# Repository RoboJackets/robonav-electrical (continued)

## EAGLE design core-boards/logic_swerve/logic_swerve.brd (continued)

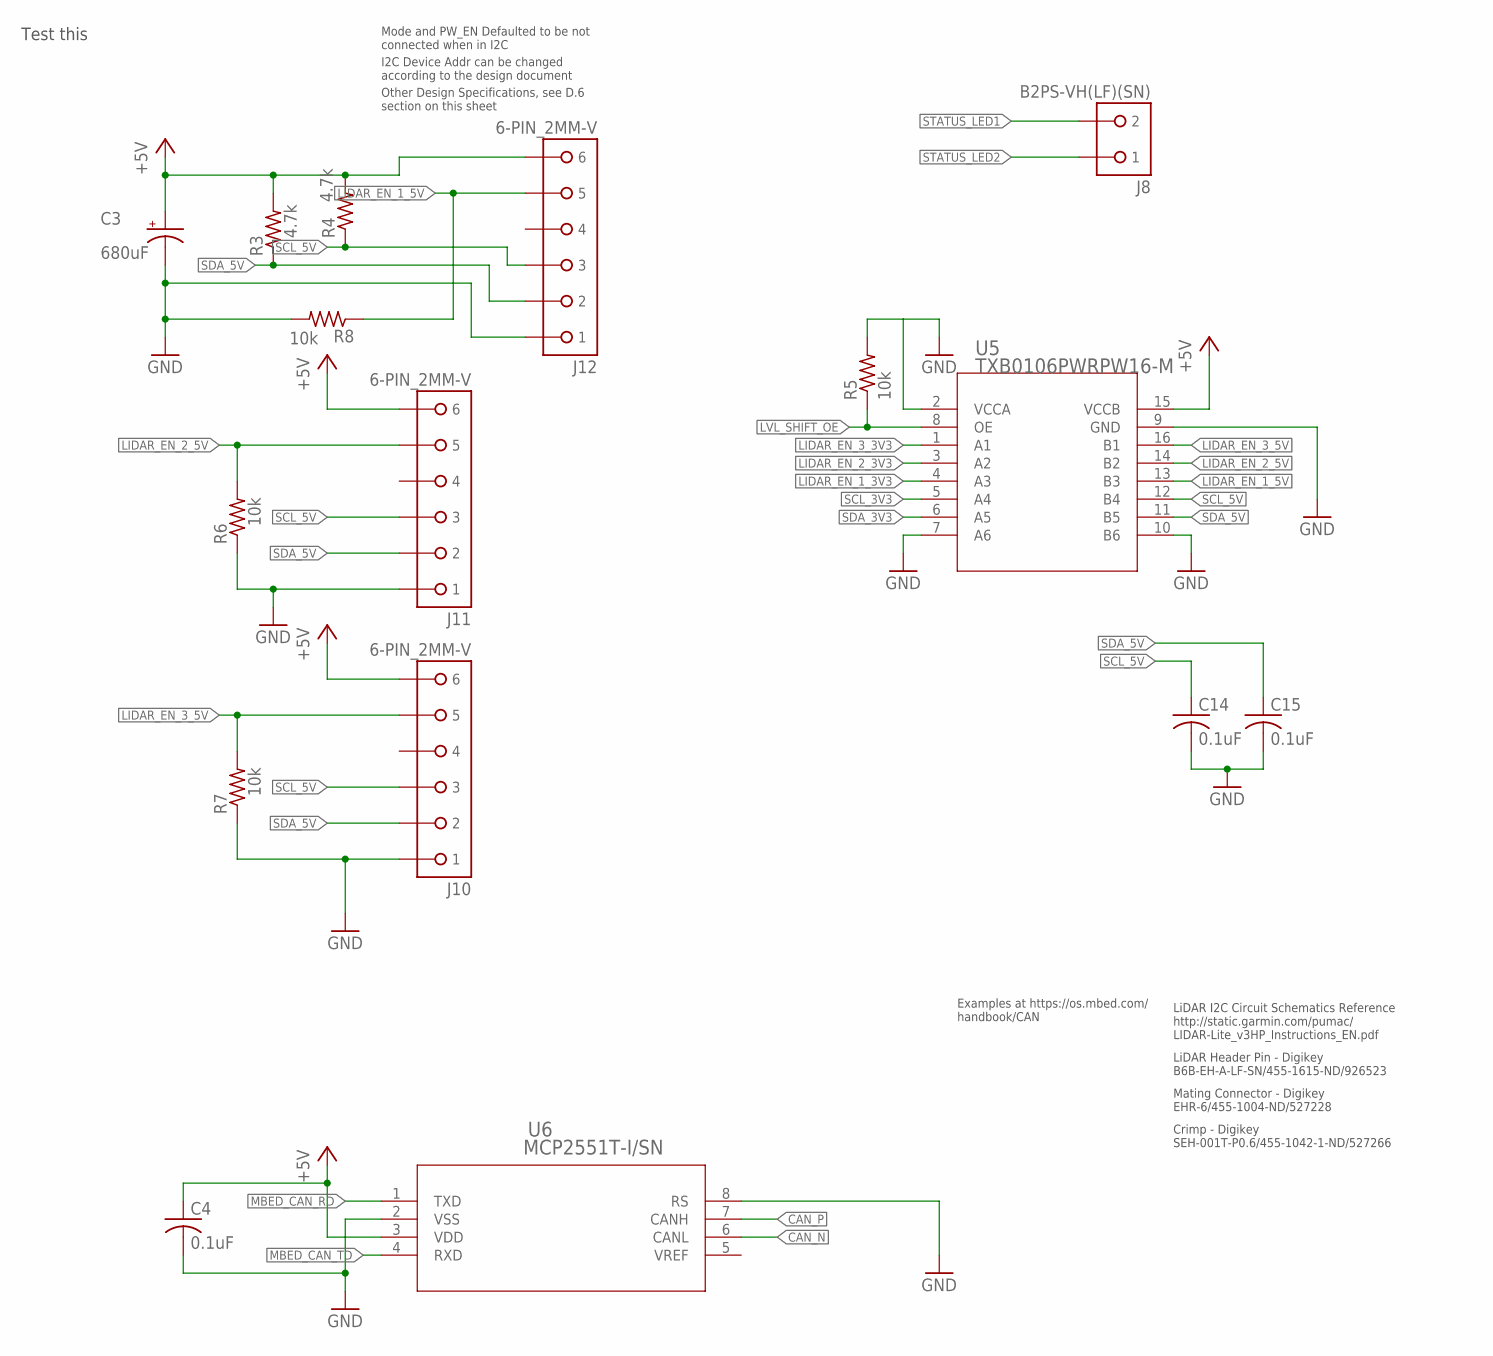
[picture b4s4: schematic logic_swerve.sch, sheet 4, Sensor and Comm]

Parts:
C3: 680uF; E5-5
C4, C14, C15: 0.1uF; C0603
J8: B2PS-VH(LF)(SN); B2PS-CENTERED
J10, J11, J12: 6-PIN_2MM-V; 2MM-6-V
R3, R4: 4.7k; R0603
R5, R6, R7, R8: 10k; R0603
U5: TXB0106PWRPW16-M; PW16-M
U6: MCP2551T-I/SN; SOIC8-N_MC

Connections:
+5V: C3.+, C4.1, J10.6, J11.6, J12.6, R3.2, R4.2, U5.15 (VCCB), U6.3 (VDD); also elsewhere on the board
CAN_N: U6.6 (CANL); also elsewhere on the board
CAN_P: U6.7 (CANH); also elsewhere on the board
GND: C3.-, C4.2, C14.2, C15.2, J10.1, J11.1, J12.1, R5.2, R6.1, R7.1, R8.2, U5.2 (VCCA), U5.7 (A6), U5.9 (GND), U5.10 (B6), U6.2 (VSS), U6.8 (RS); also elsewhere on the board
LIDAR_EN_1_3V3: U5.4 (A3); also elsewhere on the board
LIDAR_EN_1_5V: J12.5, R8.1, U5.13 (B3)
LIDAR_EN_2_3V3: U5.3 (A2); also elsewhere on the board
LIDAR_EN_2_5V: J11.5, R6.2, U5.14 (B2)
LIDAR_EN_3_3V3: U5.1 (A1); also elsewhere on the board
LIDAR_EN_3_5V: J10.5, R7.2, U5.16 (B1)
LVL_SHIFT_OE: R5.1, U5.8 (OE); also elsewhere on the board
MBED_CAN_RD: U6.1 (TXD); also elsewhere on the board
MBED_CAN_TD: U6.4 (RXD); also elsewhere on the board
SCL_3V3: U5.5 (A4); also elsewhere on the board
SCL_5V: C14.1, J10.3, J11.3, J12.3, R4.1, U5.12 (B4)
SDA_3V3: U5.6 (A5); also elsewhere on the board
SDA_5V: C15.1, J10.2, J11.2, J12.2, R3.1, U5.11 (B5)
STATUS_LED1: J8.2; also elsewhere on the board
STATUS_LED2: J8.1; also elsewhere on the board

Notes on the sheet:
LiDAR I2C Circuit Schematics Reference http://static.garmin.com/pumac/ LIDAR-Lite_v3HP_Instructions_EN.pdf
I2C Device Addr can be changed according to the design document
LiDAR Header Pin - Digikey B6B-EH-A-LF-SN/455-1615-ND/926523
Mating Connector - Digikey EHR-6/455-1004-ND/527228
Crimp - Digikey SEH-001T-P0.6/455-1042-1-ND/527266
Mode and PW_EN Defaulted to be not connected when in I2C
Examples at https://os.mbed.com/ handbook/CAN
Other Design Specifications, see D.6 section on this sheet
Test this

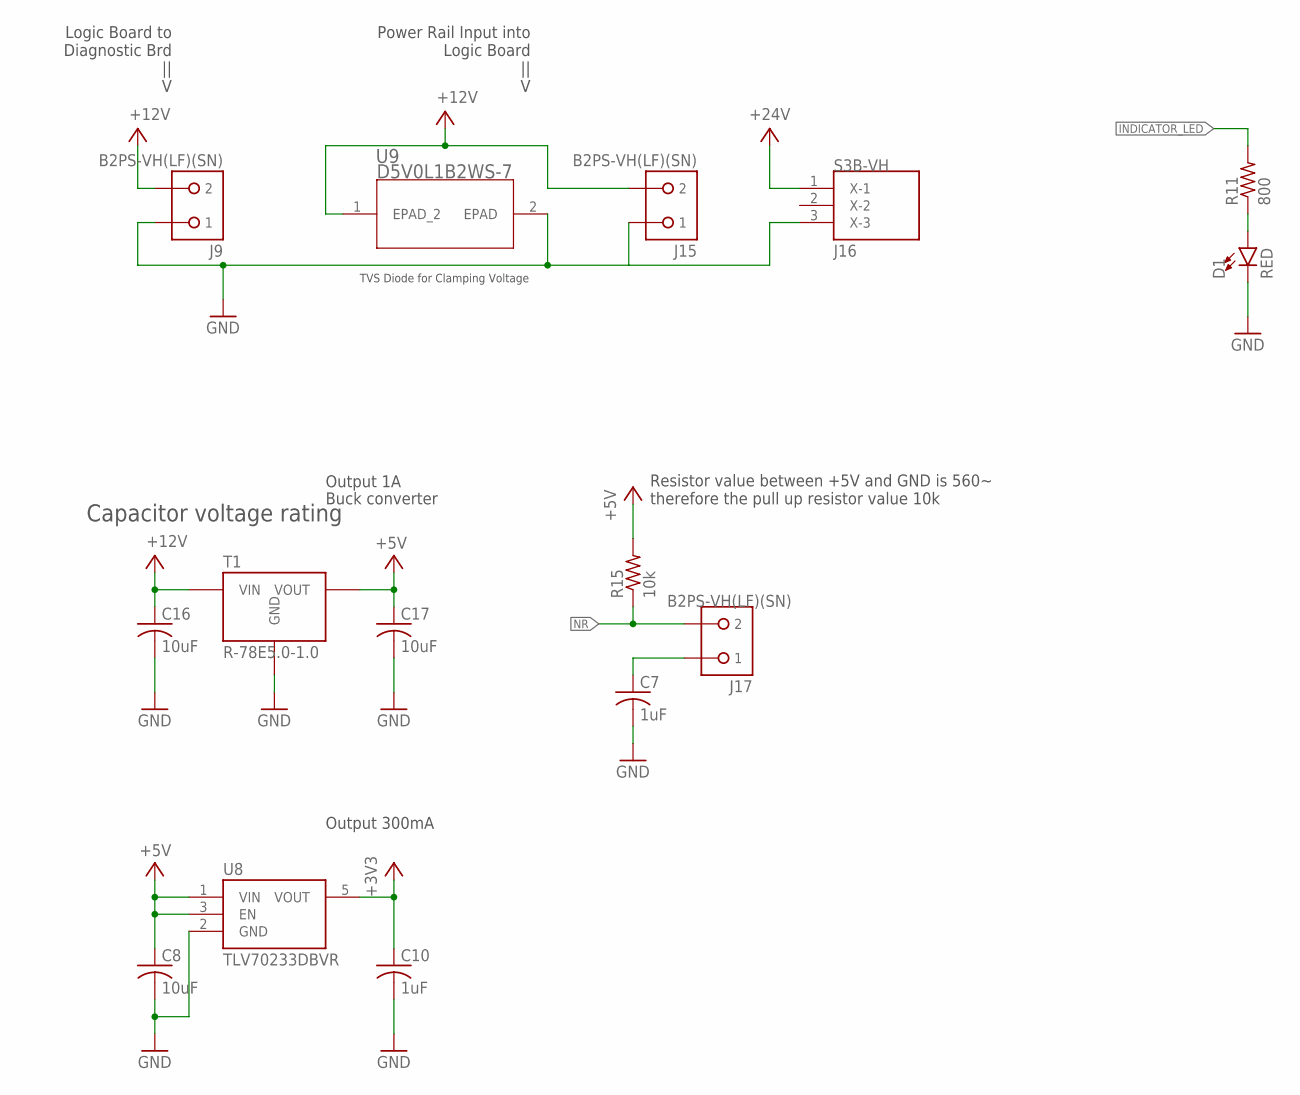
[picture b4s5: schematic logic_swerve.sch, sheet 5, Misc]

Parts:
C7, C10: 1uF; C0805
C8, C16, C17: 10uF; C0805
D1: RED; LED-0603
J9, J15, J17: B2PS-VH(LF)(SN); B2PS-CENTERED
J16: S3B-VH
R11: 800; R0603
R15: 10k; R0603
T1: R-78E5.0-1.0; R-78E
U8: TLV70233DBVR; SOT-23-5
U9: D5V0L1B2WS-7; SOD323

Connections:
+3V3: C10.1, U8.5 (VOUT); also elsewhere on the board
+5V: C8.1, C17.1, R15.2, T1.3 (VOUT), U8.1 (VIN), U8.3 (EN); also elsewhere on the board
+12V: C16.1, J9.2, J15.2, T1.1 (VIN), U9.1 (EPAD_2); also elsewhere on the board
+24V: J16.1 (X-1); also elsewhere on the board
GND: C7.2, C8.2, C10.2, C16.2, C17.2, D1.C, J9.1, J15.1, J16.3 (X-3), T1.2 (GND), U8.2 (GND), U9.2 (EPAD); also elsewhere on the board
INDICATOR_LED: R11.2; also elsewhere on the board
unnamed: D1.A, R11.1
unnamed: C7.1, J17.1
NR: J17.2, R15.1; also elsewhere on the board

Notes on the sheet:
Buck converter
Output 1A
Output 300mA
Power Rail Input into Logic Board || V
Logic Board to Diagnostic Brd || V
Capacitor voltage rating
Resistor value between +5V and GND is 560~ therefore the pull up resistor value 10k
TVS Diode for Clamping Voltage

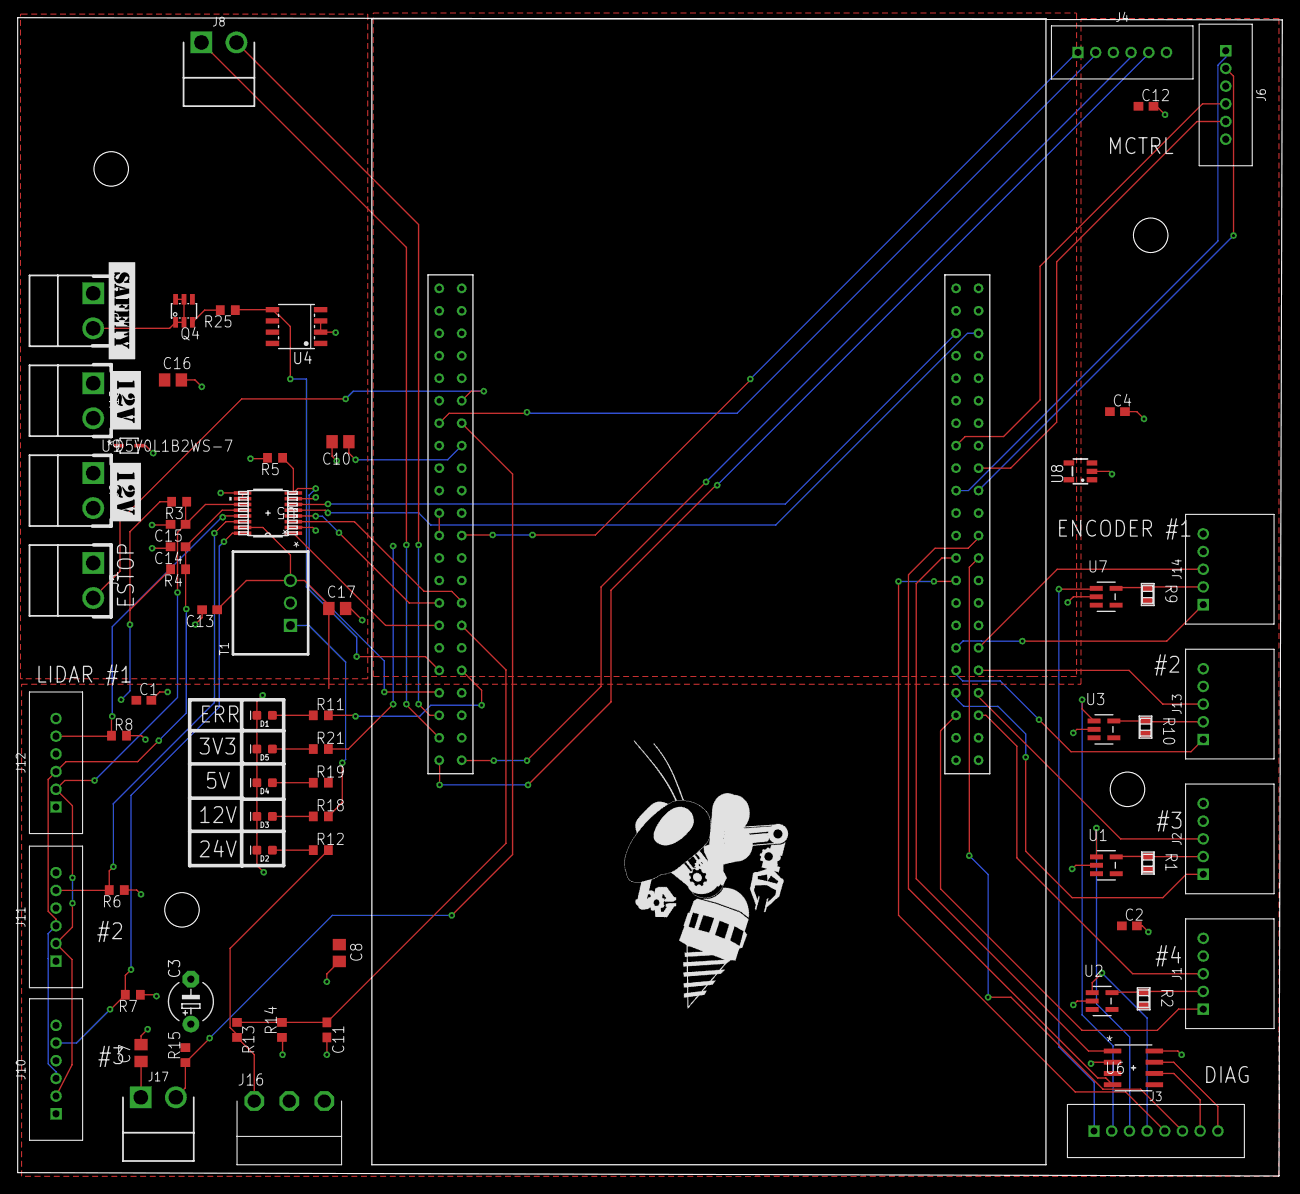
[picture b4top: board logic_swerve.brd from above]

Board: 2 copper layers, 142.9 x 130.9 mm, 75 parts (0 on the bottom side), 61 nets.

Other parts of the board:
U$2, U$3, U$4, U$5: STANDOFF-HOLE
U$6, U$7: 12V
U$10: ROBOBUZZ_1.4X
U$12: SAFETY

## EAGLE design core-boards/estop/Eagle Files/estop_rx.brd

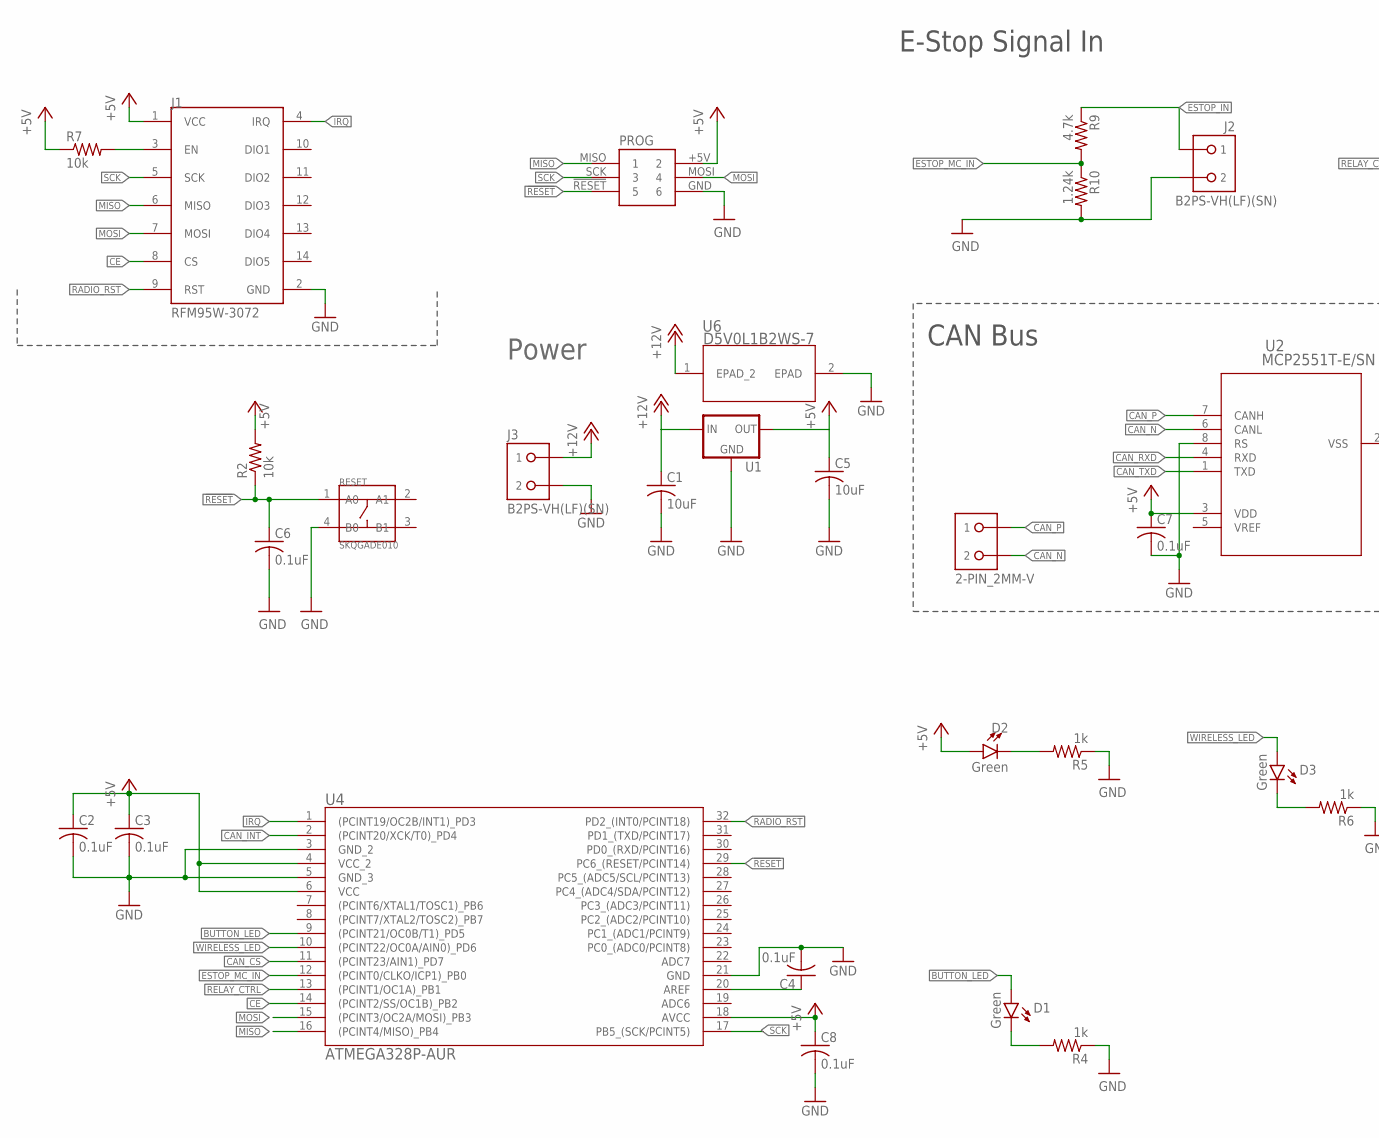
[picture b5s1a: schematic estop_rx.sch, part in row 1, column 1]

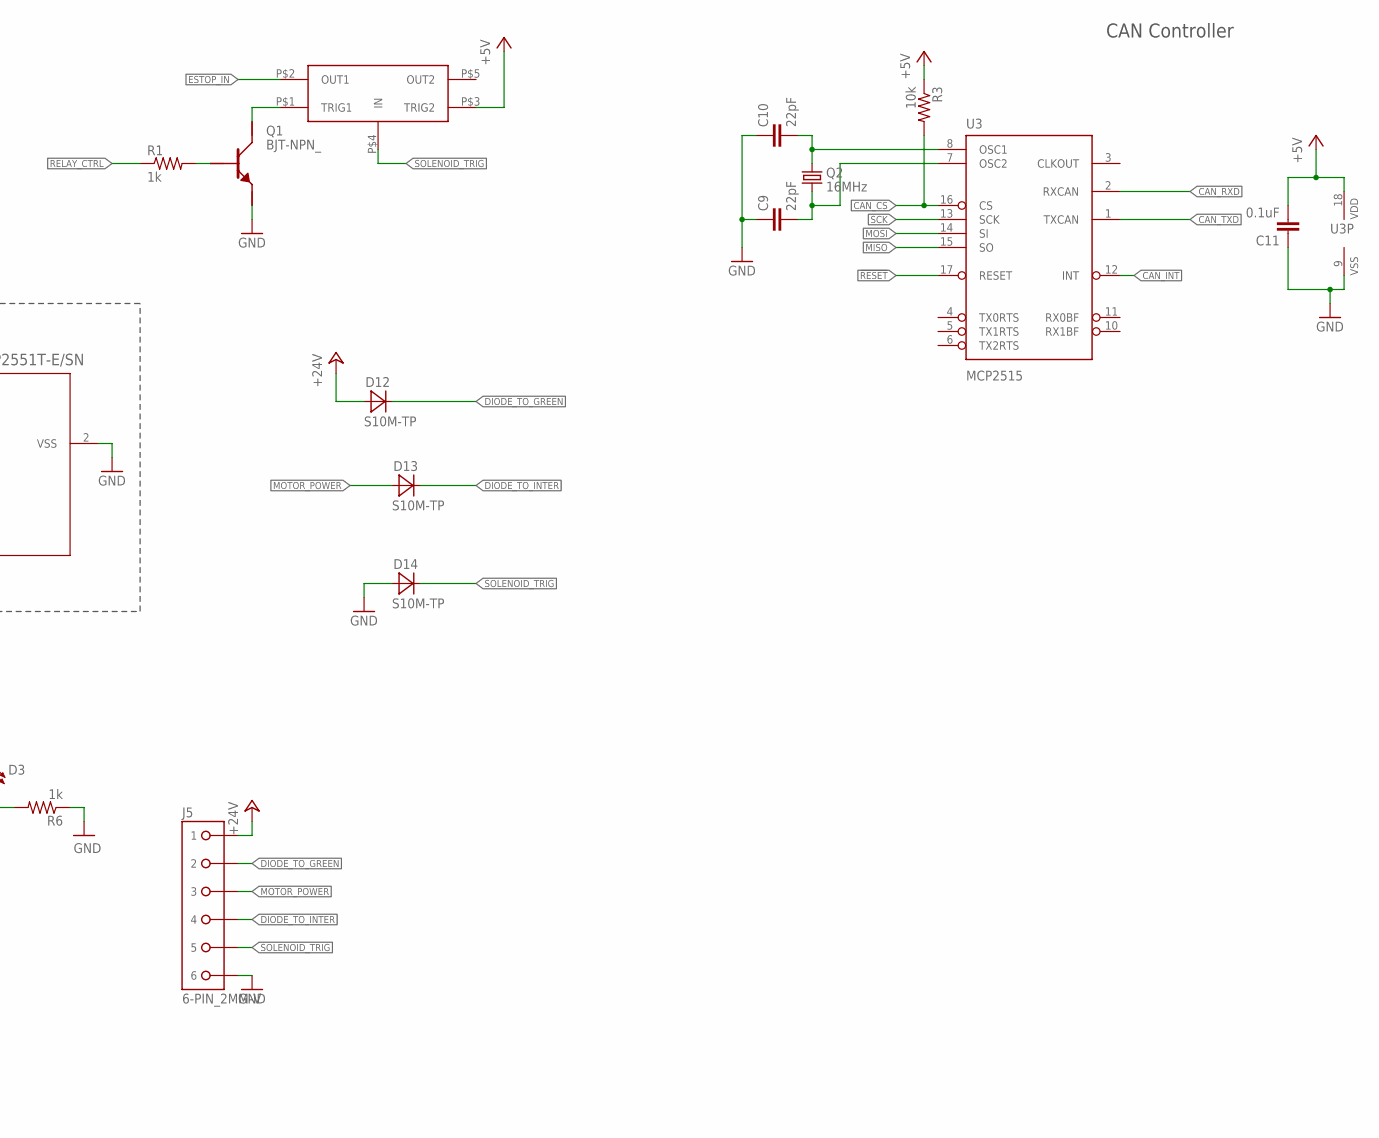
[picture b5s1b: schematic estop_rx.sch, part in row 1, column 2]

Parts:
C1, C5: 10uF; C0805
C2, C3, C4, C6, C7, C8: 0.1uF; C0603
C9, C10: 22pF; 0603-CAP
C11: 0.1uF; 0603-CAP
D1, D2, D3: Green; LED-0603
D12, D13, D14: S10M-TP; SMC
J1: RFM95W-3072
J2, J3: B2PS-VH(LF)(SN); B2PS-CENTERED
J4: 2-PIN_2MM-V; 2MM-2-V
J5: 6-PIN_2MM-V; 2MM-6-V
PROG: ICSP Connector; 2X3SHROUDED
Q1: BJT-NPN_; SOT-23-3
Q2: 16MHz; CRYSTAL-SMD-5X3
R1, R4, R5, R6: 1k; R0603
R2, R3, R7: 10k; R0603
R9: 4.7k; R0603
R10: 1.24k; R0603
RESET: SKQGADE010; SW4-SMD-5.2X5.2X1.5MM
U1: R-78E5.0-1.0CONV_R-78E5.0-1.0; CONV_R-78E5.0-1.0
U2: MCP2551T-E/SN; SOIC8-N_MC
U3: MCP2515; SO-18W
U4: ATMEGA328P-AUR
U6: D5V0L1B2WS-7; SOD323
U$1: G5LE-14

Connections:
!RESET: C6.1, PROG.!RESET (5), R2.1, RESET.1 (A0), U3.17 (RESET), U4.29 (PC6_(RESET/PCINT14))
+5V: C2.1, C3.1, C5.1, C7.1, C8.1, C11.2, D2.A, J1.1 (VCC), PROG.+5V (2), R2.2, R3.1, R7.1, U1.3 (OUT), U2.3 (VDD), U3.18 (VDD), U4.4 (VCC_2), U4.6 (VCC), U4.18 (AVCC), U$1.P$3 (TRIG2)
+12V: C1.1, J3.1, U1.1 (IN), U6.1 (EPAD_2)
+24V: D12.A, J5.1
BUTTON_LED: D1.A, U4.9 ((PCINT21/OC0B/T1)_PD5)
CAN_CS: R3.2, U3.16 (CS), U4.11 ((PCINT23/AIN1)_PD7)
CAN_INT: U3.12 (INT), U4.2 ((PCINT20/XCK/T0)_PD4)
CAN_N: J4.2, U2.6 (CANL)
CAN_P: J4.1, U2.7 (CANH)
CAN_RXD: U2.4 (RXD), U3.2 (RXCAN)
CAN_TXD: U2.1 (TXD), U3.1 (TXCAN)
CE: J1.8 (CS), U4.14 ((PCINT2/SS/OC1B)_PB2)
DIODE_TO_GREEN: D12.C, J5.2
DIODE_TO_INTER: D13.C, J5.4
ESTOP_IN: J2.1, R9.1, U$1.P$2 (OUT1)
ESTOP_MC_IN: R9.2, R10.1, U4.12 ((PCINT0/CLKO/ICP1)_PB0)
GND: C1.2, C2.2, C3.2, C4.2, C5.2, C6.2, C7.2, C8.2, C9.1, C10.1, C11.1, D14.A, J1.2 (GND), J2.2, J3.2, J5.6, PROG.GND (6), Q1.2 (E), R4.1, R5.1, R6.1, R10.2, RESET.4 (B0), U1.2 (GND), U2.2 (VSS), U2.8 (RS), U3.9 (VSS), U4.3 (GND_2), U4.5 (GND_3), U4.21 (GND), U6.2 (EPAD)
IRQ: J1.4 (IRQ), U4.1 ((PCINT19/OC2B/INT1)_PD3)
MISO: J1.6 (MISO), PROG.MISO (1), U3.15 (SO), U4.16 ((PCINT4/MISO)_PB4)
MOSI: J1.7 (MOSI), PROG.MOSI (4), U3.14 (SI), U4.15 ((PCINT3/OC2A/MOSI)_PB3)
MOTOR_POWER: D13.A, J5.3
unnamed: Q1.3 (C), U$1.P$1 (TRIG1)
unnamed: D2.C, R5.2
unnamed: D1.C, R4.2
unnamed: D3.C, R6.2
unnamed: Q1.1 (B), R1.2
unnamed: J1.3 (EN), R7.2
unnamed: C4.1, U4.20 (AREF)
unnamed: C10.2, Q2.3 (2), U3.8 (OSC1)
unnamed: C9.2, Q2.1, U3.7 (OSC2)
RADIO_RST: J1.9 (RST), U4.32 (PD2_(INT0/PCINT18))
RELAY_CTRL: R1.1, U4.13 ((PCINT1/OC1A)_PB1)
SCK: J1.5 (SCK), PROG.SCK (3), U3.13 (SCK), U4.17 (PB5_(SCK/PCINT5))
SOLENOID_TRIG: D14.C, J5.5, U$1.P$4 (IN)
WIRELESS_LED: D3.A, U4.10 ((PCINT22/OC0A/AIN0)_PD6)

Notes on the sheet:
Power
E-Stop Signal In
CAN Bus
CAN Controller

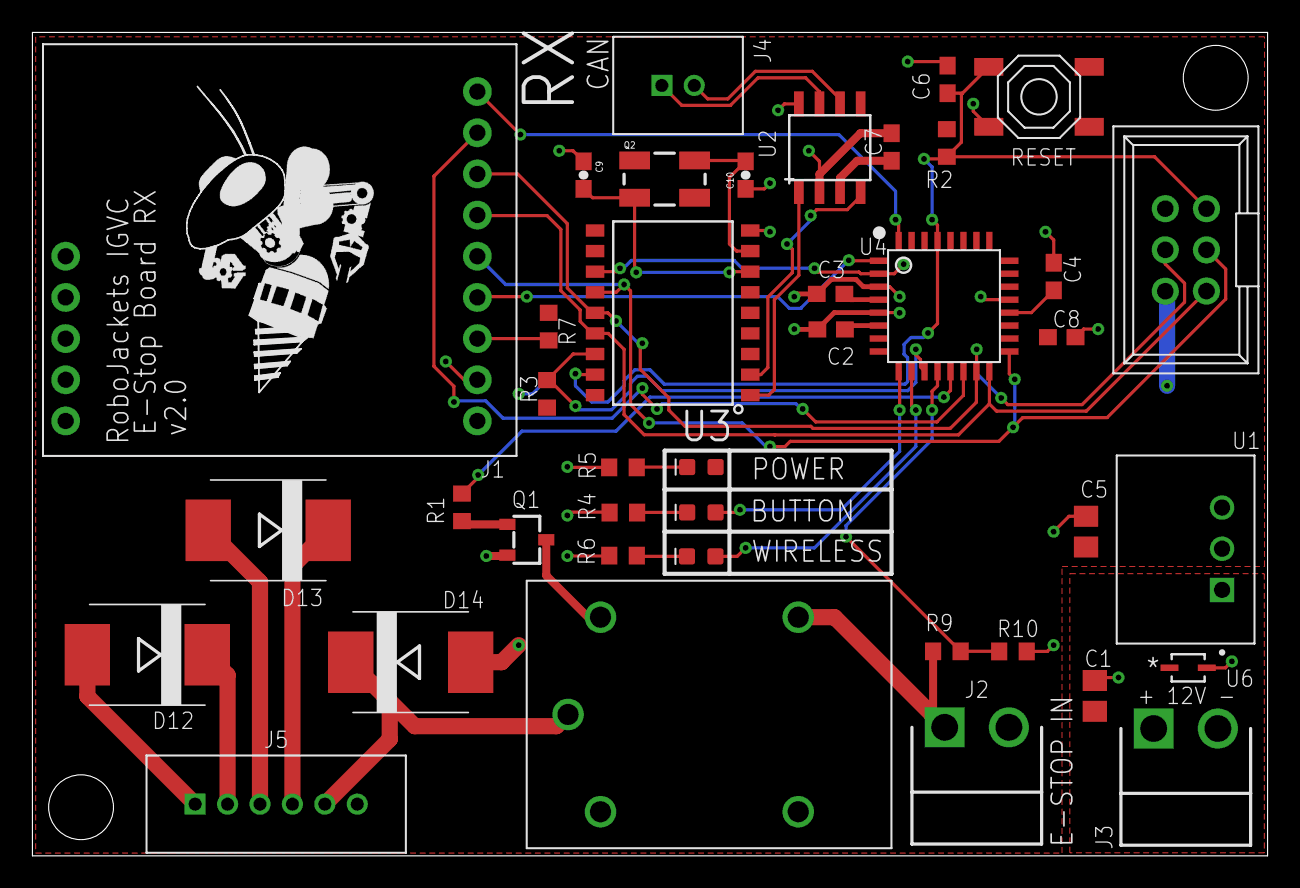
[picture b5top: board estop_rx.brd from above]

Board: 2 copper layers, 76.2 x 50.8 mm, 42 parts (1 on the bottom side), 35 nets.

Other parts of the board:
U$2: ROBOBUZZ_1.0X2

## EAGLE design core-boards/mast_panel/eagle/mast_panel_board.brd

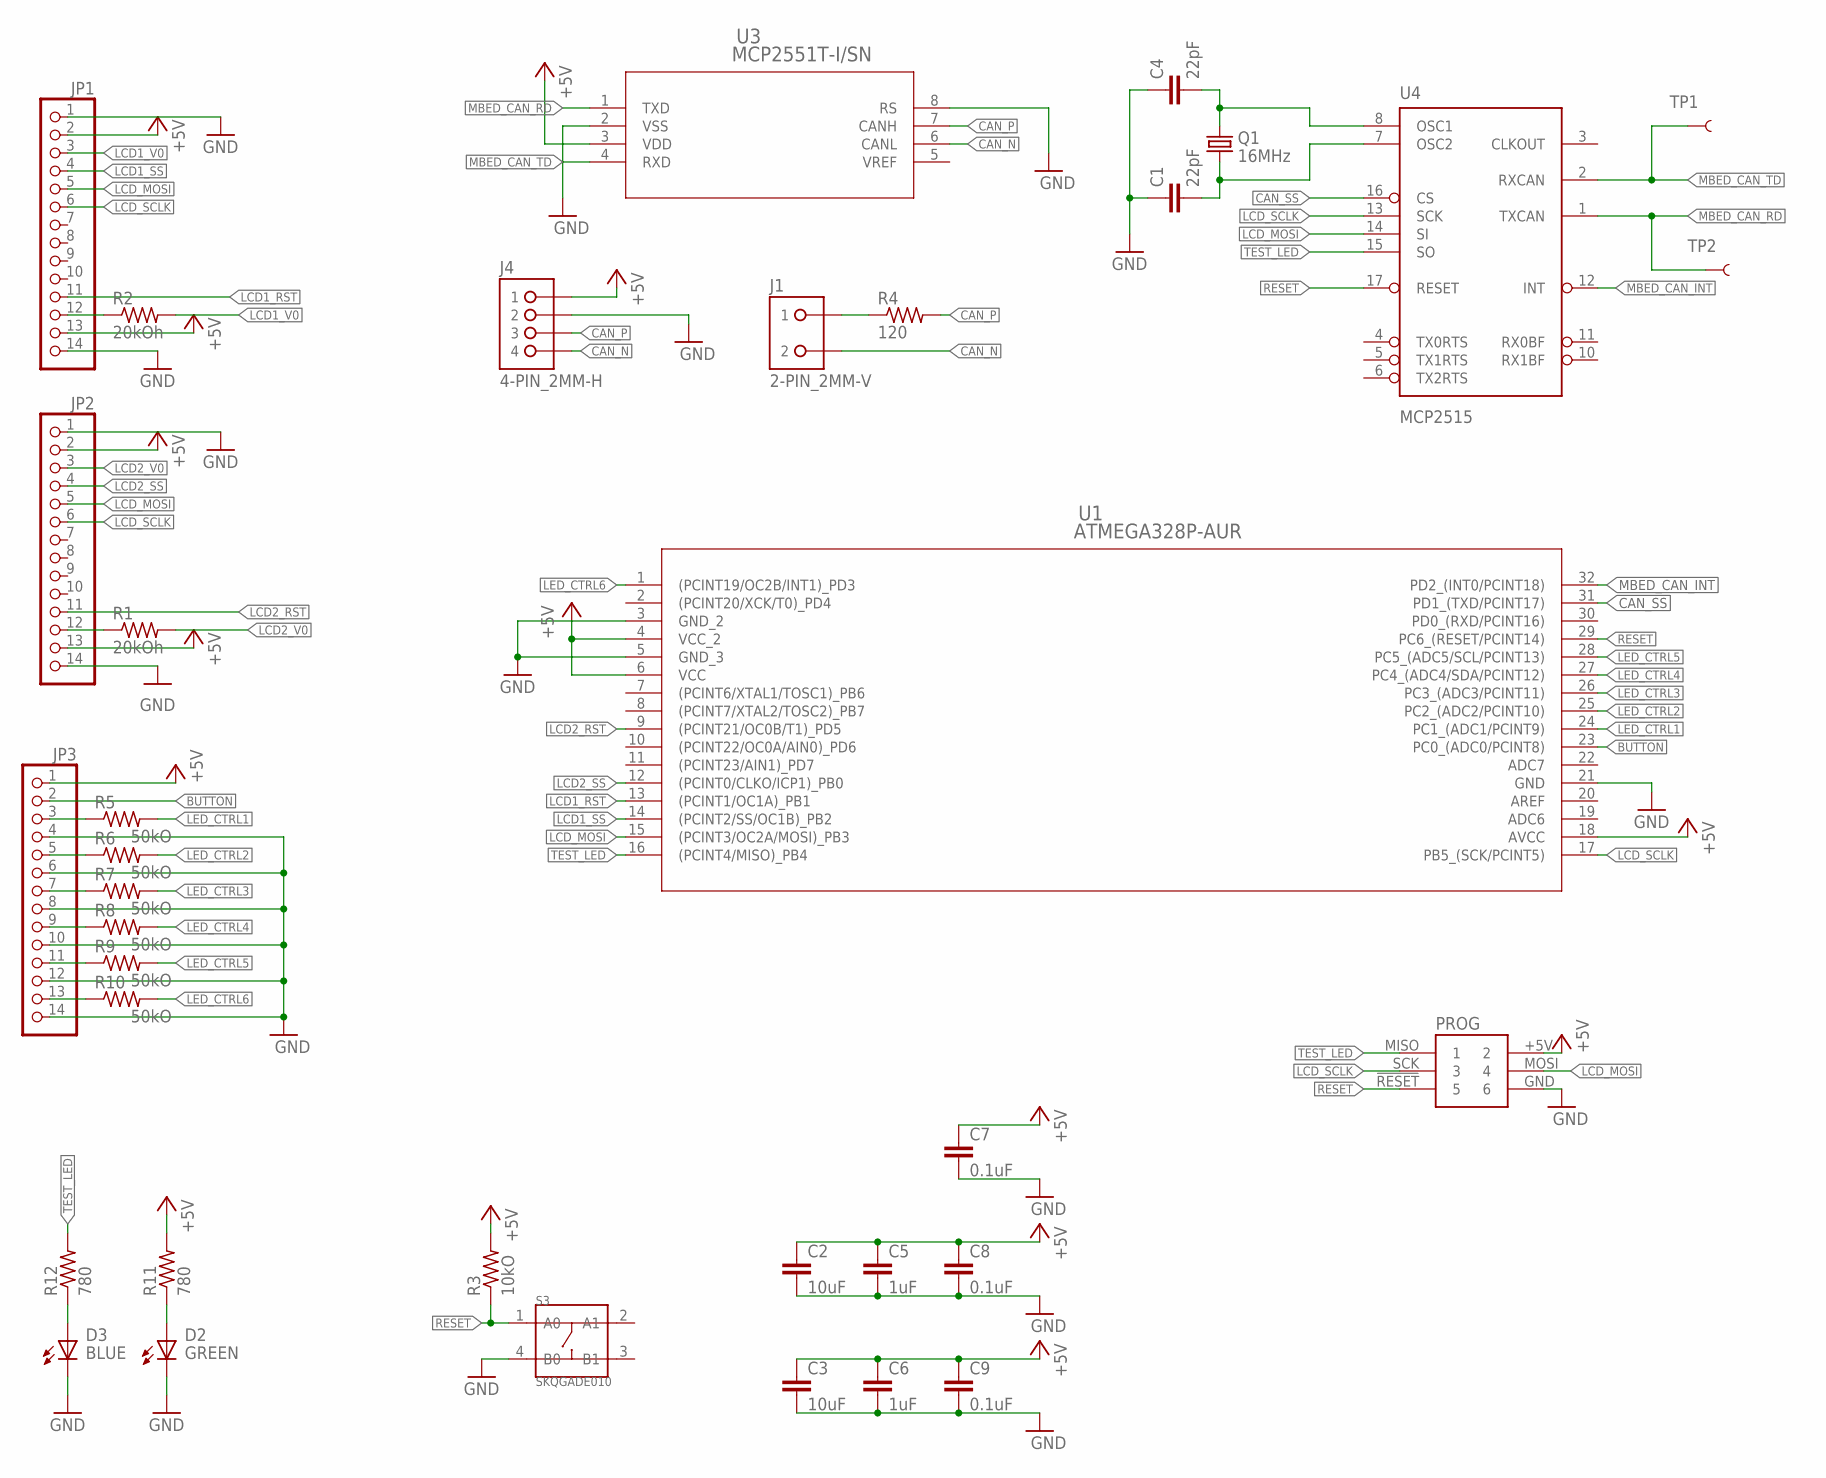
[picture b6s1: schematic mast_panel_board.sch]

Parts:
C1, C4: 22pF; 0603-CAP
C2, C3: 10uF; C0805
C5, C6: 1uF; C0603
C7, C8, C9: 0.1uF; C0402
D2: GREEN; CHIP-LED0603
D3: BLUE; CHIP-LED0603
J1: 2-PIN_2MM-V; 2MM-2-V
J4: 4-PIN_2MM-H; 2MM-4-H
JP1, JP2, JP3: PINHD-1X14; 1X14
PROG: ICSP Connector; 2X3SHROUDED
Q1: 16MHz; CRYSTAL-SMD-5X3
R1, R2: 20kOh; R0603
R3: 10kO; R0603
R4: 120; R0603
R5, R6, R7, R8, R9, R10: 50kO; R0805
R11, R12: 780; R0402
S3: SKQGADE010; SW4-SMD-5.2X5.2X1.5MM
TP1, TP2: TEST-POINT3X5; PAD.03X.05
U1: ATMEGA328P-AUR; 32A
U3: MCP2551T-I/SN; SOIC8-N_MC
U4: MCP2515; SO-18W

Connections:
+5V: C2.1, C3.1, C5.1, C6.1, C7.1, C8.1, C9.1, J4.1, JP1.2, JP1.13, JP2.2, JP2.13, JP3.1, PROG.+5V (2), R3.2, R11.2, U1.4 (VCC_2), U1.6 (VCC), U1.18 (AVCC), U3.3 (VDD)
BUTTON: JP3.2, U1.23 (PC0_(ADC0/PCINT8))
CAN_N: J1.2, J4.4, U3.6 (CANL)
CAN_P: J4.3, R4.2, U3.7 (CANH)
CAN_SS: U1.31 (PD1_(TXD/PCINT17)), U4.16 (CS)
GND: C1.1, C2.2, C3.2, C4.1, C5.2, C6.2, C7.2, C8.2, C9.2, D2.C (K), D3.C (K), J4.2, JP1.1, JP1.14, JP2.1, JP2.14, JP3.4, JP3.6, JP3.8, JP3.10, JP3.12, JP3.14, PROG.GND (6), S3.4 (B0), U1.3 (GND_2), U1.5 (GND_3), U1.21 (GND), U3.2 (VSS), U3.8 (RS)
LCD1_RST: JP1.11, U1.13 ((PCINT1/OC1A)_PB1)
LCD1_SS: JP1.4, U1.14 ((PCINT2/SS/OC1B)_PB2)
LCD1_V0: JP1.3, R2.2
LCD2_RST: JP2.11, U1.9 ((PCINT21/OC0B/T1)_PD5)
LCD2_SS: JP2.4, U1.12 ((PCINT0/CLKO/ICP1)_PB0)
LCD2_V0: JP2.3, R1.2
LCD_MOSI: JP1.5, JP2.5, PROG.MOSI (4), U1.15 ((PCINT3/OC2A/MOSI)_PB3), U4.14 (SI)
LCD_SCLK: JP1.6, JP2.6, PROG.SCK (3), U1.17 (PB5_(SCK/PCINT5)), U4.13 (SCK)
LED1: JP3.3, R5.1
LED2: JP3.5, R6.1
LED3: JP3.7, R7.1
LED4: JP3.9, R8.1
LED5: JP3.11, R9.1
LED6: JP3.13, R10.1
LED_CTRL1: R5.2, U1.24 (PC1_(ADC1/PCINT9))
LED_CTRL2: R6.2, U1.25 (PC2_(ADC2/PCINT10))
LED_CTRL3: R7.2, U1.26 (PC3_(ADC3/PCINT11))
LED_CTRL4: R8.2, U1.27 (PC4_(ADC4/SDA/PCINT12))
LED_CTRL5: R9.2, U1.28 (PC5_(ADC5/SCL/PCINT13))
LED_CTRL6: R10.2, U1.1 ((PCINT19/OC2B/INT1)_PD3)
MBED_CAN_INT: U1.32 (PD2_(INT0/PCINT18)), U4.12 (INT)
MBED_CAN_RD: TP2.P$1, U3.1 (TXD), U4.1 (TXCAN)
MBED_CAN_TD: TP1.P$1, U3.4 (RXD), U4.2 (RXCAN)
unnamed: J1.1, R4.1
unnamed: JP1.12, R2.1
unnamed: D2.A, R11.1
unnamed: D3.A, R12.1
unnamed: JP2.12, R1.1
unnamed: C4.2, Q1.3 (2), U4.8 (OSC1)
unnamed: C1.2, Q1.1, U4.7 (OSC2)
RESET: PROG.!RESET (5), R3.1, S3.1 (A0), U1.29 (PC6_(RESET/PCINT14)), U4.17 (RESET)
TEST_LED: PROG.MISO (1), R12.2, U1.16 ((PCINT4/MISO)_PB4), U4.15 (SO)
VDD: U4.18 (VDD)
VSS: U4.9 (VSS)

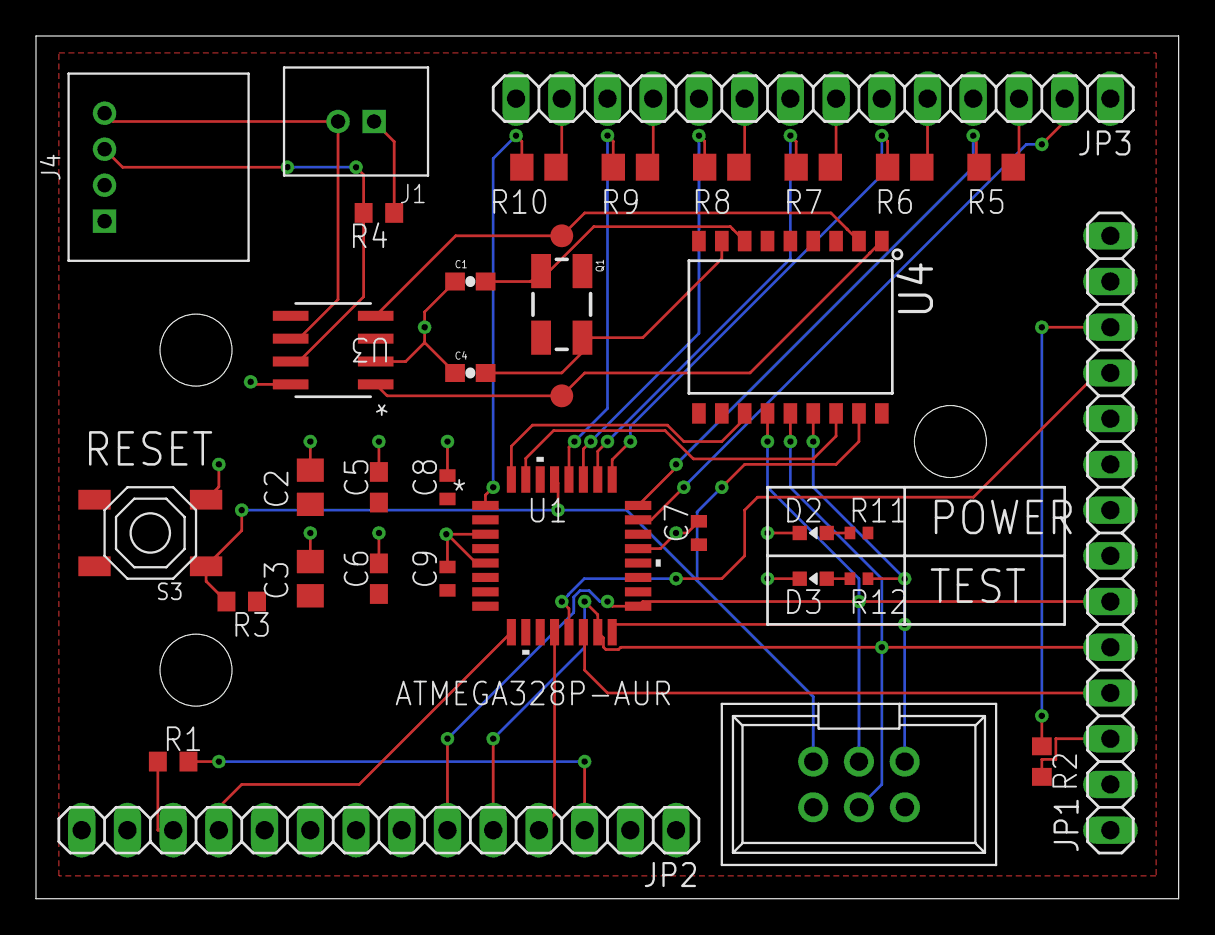
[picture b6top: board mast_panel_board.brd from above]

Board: 2 copper layers, 63.5 x 47.9 mm, 36 parts (0 on the bottom side), 38 nets.
